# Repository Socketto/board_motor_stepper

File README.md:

This board, designed with KiCad 9.0 and programmed with MPLAB X, is capable of driving a bipolar stepper motor (such as those used in printers).

It is programmed to be controlled via a standard RS-485 interface with a custom protocol but is already prepared to be integrated into a larger network of boards with hardware addressing and a standard protocol (such as Modbus).  

Currently, to control the motor, simply send the character '1' to move it clockwise or '2' to move it counterclockwise. As feedback, the board will send back the character '5' (ACK).

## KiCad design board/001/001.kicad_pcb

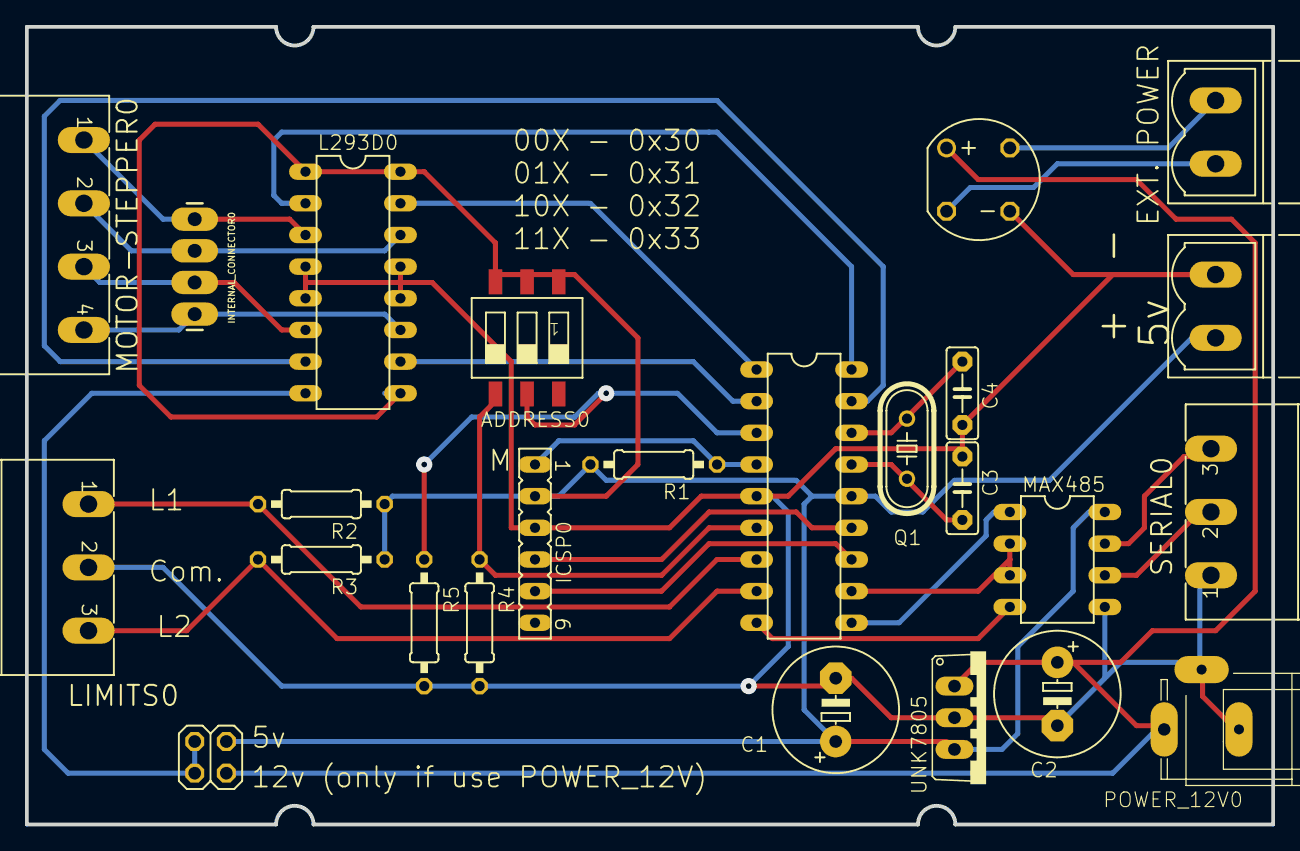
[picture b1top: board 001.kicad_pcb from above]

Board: 16 copper layers, 100.0 x 64.0 mm, 25 parts (0 on the bottom side), 23 nets.

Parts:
ADDRESS0: SMS-003_362
C1, C2: E5-10,5
C3, C4: C5B2.5
E$1, E$2: MSTBV2R_175
E$3: RB1A_336
ICSP0: FE06
INTERNAL_CONNECTOR0: 1X04_LONGPADS_513
L293D0: DIL16_80
LIMITS0: MSTBA3_176
MAX485: DIL08_80
MOTOR-STEPPER0: MSTBA4_176
PIC18F1: DIL18
POWER_12V0: SPC4077_154
Q1: HC49_S
R1, R2, R3, R4, R5: 10k; 0207_10
SERIAL0: MSTBA3_176
UNK12V_5V0: 2X02_325
UNK7805: TO220V

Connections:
S$1: L293D0.8, UNK12V_5V0.1, UNK12V_5V0.2
S$5: C3.1, PIC18F1.15
S$6: C4.2, PIC18F1.16
S$7: MAX485.2, MAX485.3, PIC18F1.11
S$9: C2.-, MAX485.5
S$11: ICSP0.1, PIC18F1.4, R1.1
S$12: L293D0.2, PIC18F1.18
S$13: PIC18F1.6, R4.1
S$14: MAX485.4, PIC18F1.9
S$15: C1.-, C3.2, C4.1, E$2.2, E$3.-, ICSP0.3, L293D0.4, L293D0.5, L293D0.12, L293D0.13, PIC18F1.3, PIC18F1.5, R5.1
S$17: ICSP0.5, PIC18F1.12
S$20: L293D0.10, PIC18F1.2
S$21: C1.+, E$2.1, ICSP0.2, L293D0.1, L293D0.9, L293D0.16, PIC18F1.14, R1.2, R2.1, R3.1, UNK12V_5V0.4
S$22: INTERNAL_CONNECTOR0.2, L293D0.6, MOTOR-STEPPER0.3
S$24: INTERNAL_CONNECTOR0.4, L293D0.3
S$25: L293D0.7, PIC18F1.17
S$26: INTERNAL_CONNECTOR0.3, L293D0.14, MOTOR-STEPPER0.2
S$27: E$1.2, E$3.AC1
S$28: INTERNAL_CONNECTOR0.1, L293D0.11, MOTOR-STEPPER0.4
S$29: PIC18F1.7, R2.2
S$30: PIC18F1.8, R3.2
S$31: E$1.1, E$3.AC2
S$32: E$3.+, UNK7805.1

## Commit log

2025-03-07 [ADD] Add first revision
2025-03-07 [UPD] Update README.md
2025-03-07 [ADD] Add KiCad 9.0 project
2025-03-07 [UPD] Update gitignore
2025-04-18 [UPD] Update board
